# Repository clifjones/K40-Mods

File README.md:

# K40-Mods
Hardware modifications to my Chinese K40 CO2 LASER cutter

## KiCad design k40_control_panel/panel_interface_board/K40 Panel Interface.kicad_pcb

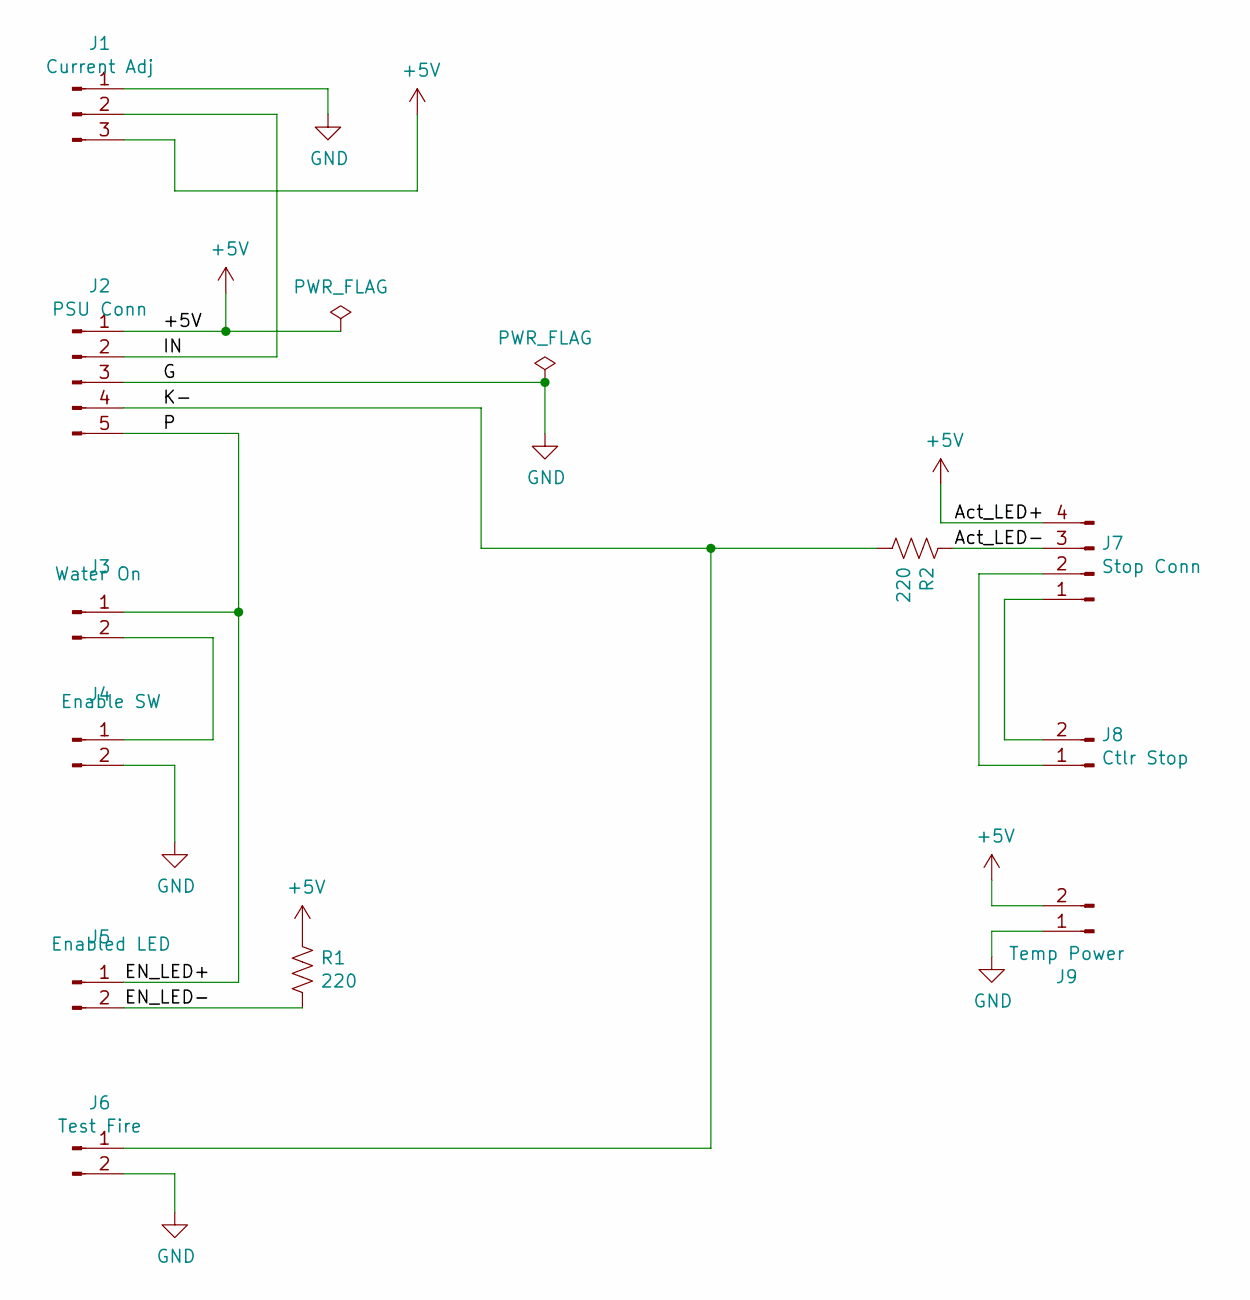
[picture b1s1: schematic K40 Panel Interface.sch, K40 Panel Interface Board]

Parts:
J1: Current Adj; Pin_Header_Straight_1x03_Pitch2.54mm
J2: PSU Conn; Pin_Header_Straight_1x05_Pitch2.54mm
J3: Water On; Pin_Header_Straight_1x02_Pitch2.54mm
J4: Enable SW; Pin_Header_Straight_1x02_Pitch2.54mm
J5: Enabled LED; Pin_Header_Straight_1x02_Pitch2.54mm
J6: Test Fire; Pin_Header_Straight_1x02_Pitch2.54mm
J7: Stop Conn; Pin_Header_Straight_1x04_Pitch2.54mm
J8: Ctlr Stop; Pin_Header_Straight_1x02_Pitch2.54mm
J9: Temp Power; Pin_Header_Straight_1x02_Pitch2.54mm
R1, R2: 220; R_Box_L8.4mm_W2.5mm_P5.08mm

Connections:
+5V: J1.3, J2.1, J7.4, J9.2, R1.1
/Act_LED-: J7.3, R2.1
/EN_LED+: J2.5, J3.1, J5.1
/EN_LED-: J5.2, R1.2
/IN: J1.2, J2.2
/K-: J2.4, J6.1, R2.2
GND: J1.1, J2.3, J4.2, J6.2, J9.1
unnamed: J3.2, J4.1
unnamed: J7.1, J8.2
unnamed: J7.2, J8.1

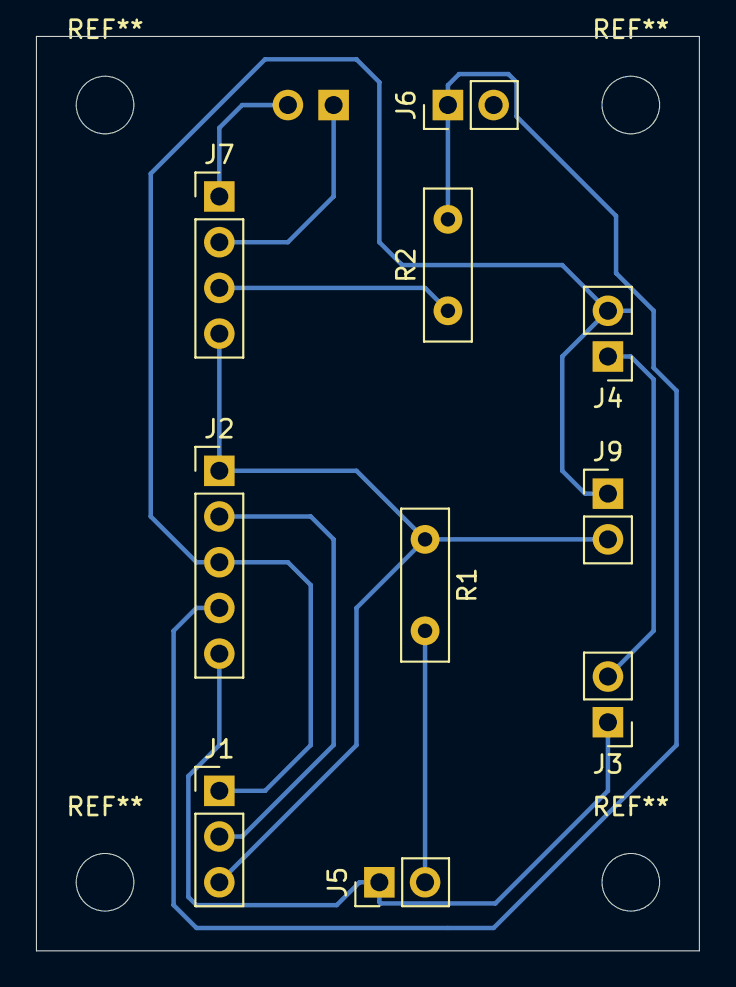
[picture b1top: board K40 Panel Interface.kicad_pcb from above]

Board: 2 copper layers, 36.8 x 50.8 mm, 11 parts (1 on the bottom side), 10 nets.

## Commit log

2019-12-23 Added Lightburn project for faceplate and KiCAD files for panel wiring
